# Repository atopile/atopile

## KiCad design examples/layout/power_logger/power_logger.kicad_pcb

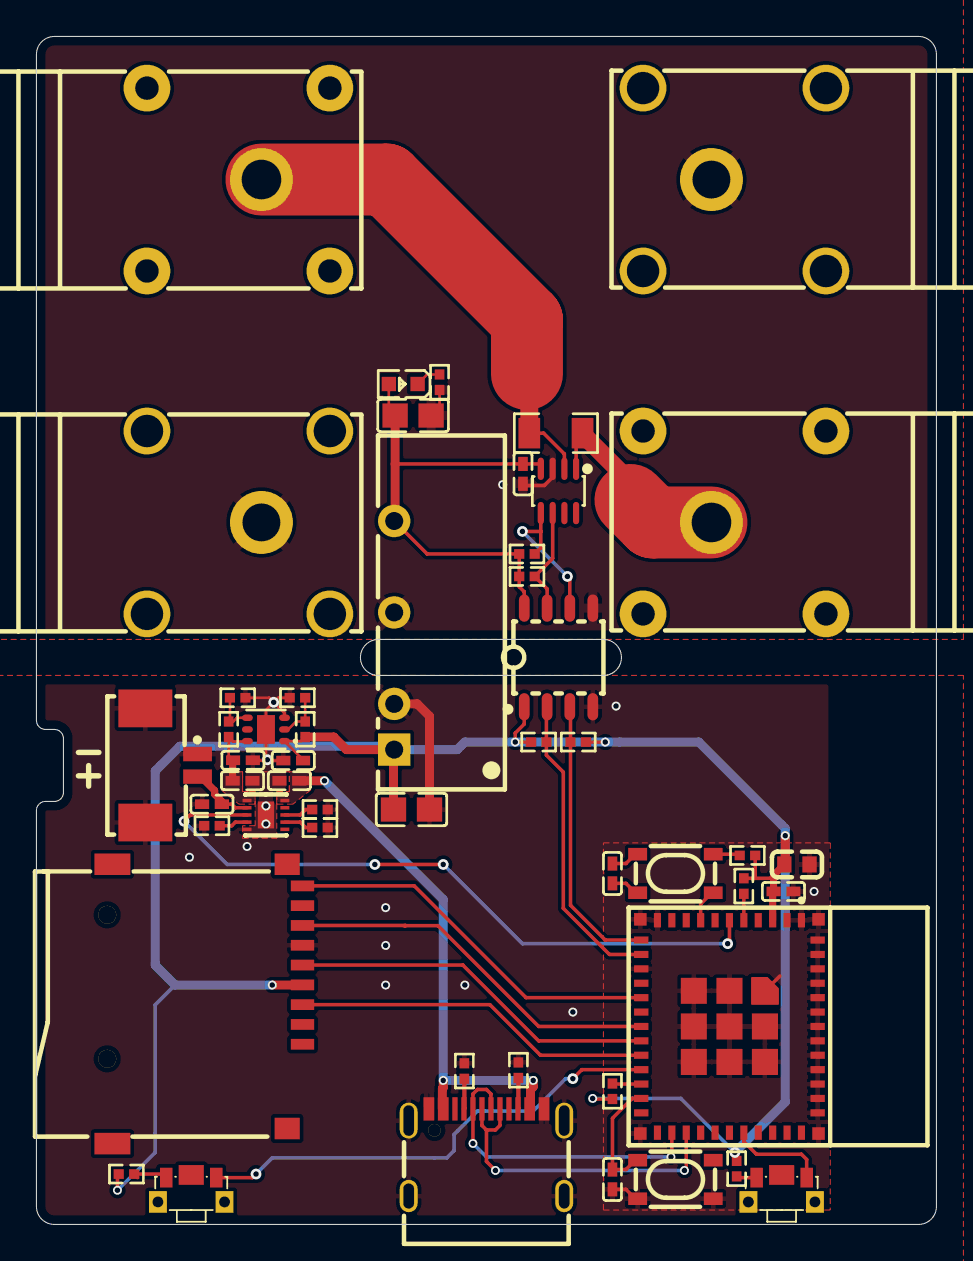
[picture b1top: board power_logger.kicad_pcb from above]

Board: 2 copper layers, 50.0 x 66.0 mm, 51 parts (1 on the bottom side), 38 nets.

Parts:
B1: EEMB_BATTERY_LP402535
C1, C3, C5, C6: 1µF ±10% 25V X5R; C0402
C2: 10µF ±20% 6.3V X5R; C0402
C4, C7, C8, C12: 100nF ±10% 16V X7R; C0402
C9: 22µF ±20% 6.3V X5R; C0603
C10: 2.2µF ±10% 25V X7R; C0805
C11: 10µF ±10% 25V X5R; C0805
Card1: TF-SMD_TF-01A
D1: LED0603-RD
J1, J3: ANT-TH_L33.0-W12.0_BLACK
J2, J4: ANT-TH_L33.0-W12.0_RED
R1, R2, R4, R5, R10, R11, R12, R13, R14, R15, R19, R20: 10kΩ ±1% 62.5mW; R0402
R3, R7: 100kΩ ±1% 62.5mW; R0402
R6: 0Ω 250mW; R1206
R8: 150kΩ ±1% 62.5mW; R0402
R9, R18: 2kΩ ±1% 62.5mW; R0402
R16, R17: 4.7kΩ ±1% 62.5mW; R0402
SW1, SW2: KEY-SMD_SKTDLDE010
SW3, SW4: KEY-SMD_4P-L4.2-W3.2-P2.20-LS4.6
U1: WSON-10_L2.2-W2.0-P0.40-BL-EP_TI_DLH0010A
U2: SOT-23-8_L2.9-W1.6-P0.65-LS2.8-BR
U3: WSON-6_L2.0-W2.0-P0.65-TL-EP
U4: WIFIM-SMD_ESP32-C3-MINI-1
U5: PWRM-TH_BXXXXS-2WR3
U6: SOIC-8_L4.9-W3.9-P1.27-LS6.0-TL
U7: CONN-SMD_532610271
USB1: USB-C-SMD_KH-TYPE-C-16P

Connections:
A5: R16.1, USB1.A5
B5: R17.1, USB1.B5
CD: Card1.9, U4.16
EN: R7.1, R8.2, U3.4
FB: R9.1, R10.2, U3.2
GND: Card1.10, Card1.11, Card1.12, Card1.13
ILIM_VSET: R3.1, U1.7
INneg: J4.5, R6.2, U2.2
INpos: J2.5, R6.1, U2.1
ISET: R1.1, U1.8
SCL2: R19.1, U2.5, U6.6
SDA2: R20.1, U2.6, U6.7
cathode: D1.1, R18.1
gnd: C1.2, C2.2, C3.2, C5.2, C6.2, C7.1, C9.2, C10.2, C12.2, Card1.6, R1.2, R2.2, R3.2, R7.2, R9.2, R16.2, R17.2, SW3.1, SW3.2, U1.5, U1.11, U3.3, U3.7, U4.1, U4.2, U4.11, U4.14, U4.36, U4.37, U4.38, U4.39, U4.40, U4.41, U4.42, U4.43, U4.44, U4.45, U4.46, U4.47, U4.48, U4.49, U4.50, U4.51, U4.52, U4.53, U5.2, U6.4, U7.1, U7.3, U7.4, USB1.1, USB1.2, USB1.3, USB1.4, USB1.A1, USB1.A12, USB1.B1, USB1.B12
gnd-1: C4.2, C11.2, J1.5, J3.5, R18.2, U2.3, U5.4, U6.5
hv: C5.1, C9.1, C10.1, C12.1, Card1.4, R4.2, R5.2, R10.1, R11.2, R12.2, R13.2, R14.2, R15.2, U3.1, U4.3, U5.1, U6.1
hv-1: C4.1, C11.1, D1.2, R19.2, R20.2, U2.4, U5.6, U6.8
hv-2: C3.1, U1.10, USB1.A4, USB1.A9, USB1.B4, USB1.B9
hv-3: C1.1, U1.2, U7.2
hv-4: C2.1, C6.1, R8.1, U1.1, U3.6
input: C8.1, R13.1, SW4.1, SW4.2
input-1: R5.1, SW2.1
input-2: R4.1, SW1.1
line: Card1.5, U4.19
line-1: Card1.3, U4.20
line-2: Card1.7, U4.18
line-3: R14.1, U4.12, U6.3
line-4: R15.1, U4.13, U6.2
line-5: R11.1, U4.5
line-6: U1.3, U4.6
line-7: U4.26, USB1.A7, USB1.B7
line-8: U4.27, USB1.A6, USB1.B6
line-10: R12.1, U4.22
nCE: R2.1, U1.4
output: C8.2, SW4.3, SW4.4, U4.8
output-1: SW2.2, U4.21
output-2: SW1.2, U4.31
output-3: C7.2, SW3.3, SW3.4, U4.23

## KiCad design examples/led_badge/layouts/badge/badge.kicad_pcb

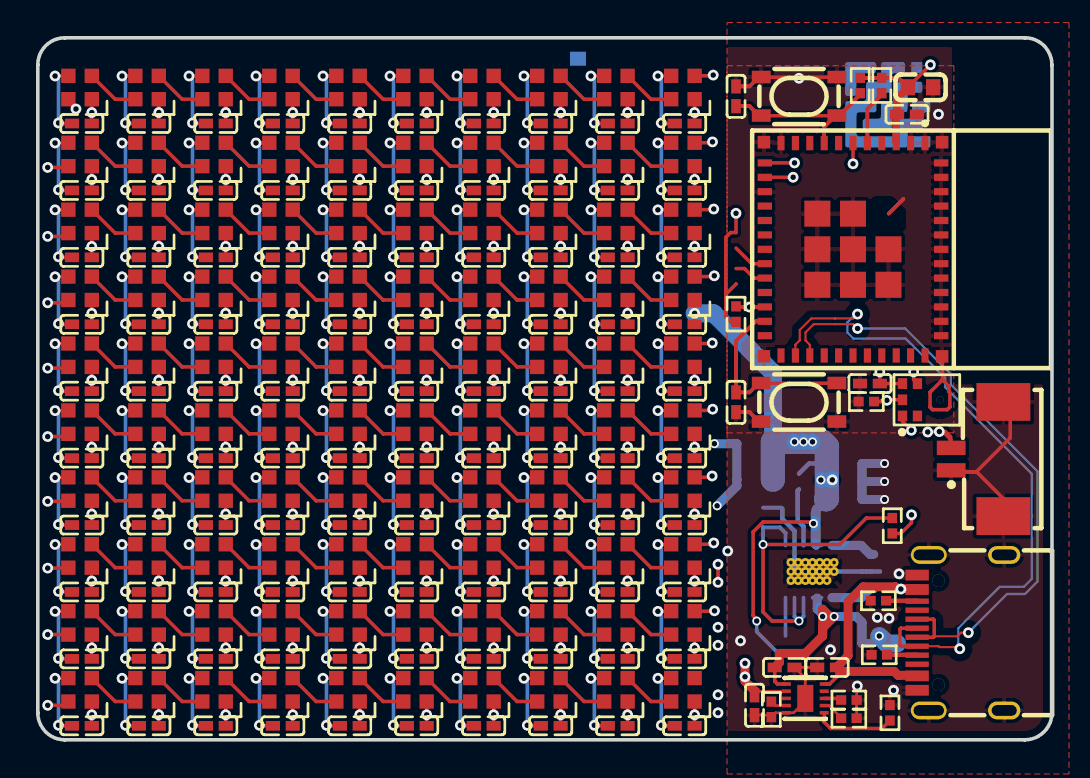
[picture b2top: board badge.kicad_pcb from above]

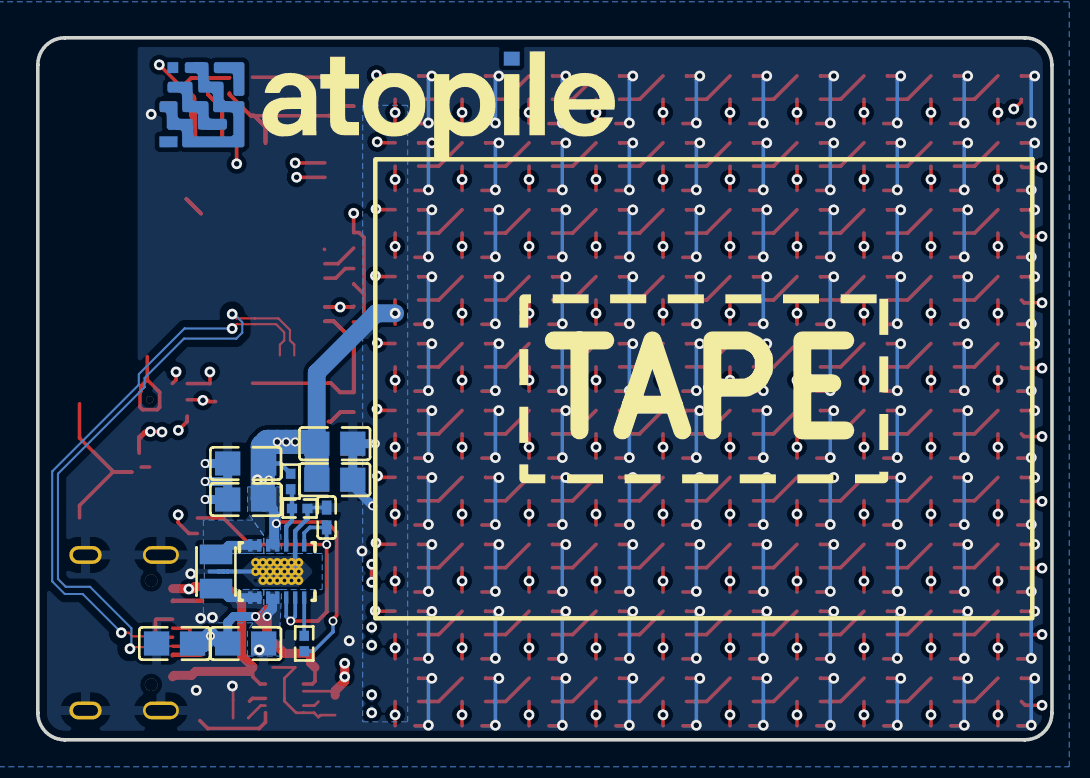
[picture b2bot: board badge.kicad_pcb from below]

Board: 4 copper layers, 56.3 x 39.0 mm, 240 parts (14 on the bottom side), 124 nets.

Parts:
B1: EEMB_BATTERY_LP402535
C1, C2: 10µF ±10% 25V X5R; C0805
C3, C4, C110, C111: 22µF ±20% 6.3V X5R; C0805
C5, C6, C7, C8, C9, C10, C11, C12, C13, C14, C15, C16, C17, C18, C19, C20, C21, C22, C23, C24, C25, C26, C27, C28, C29, C30, C31, C32, C33, C34, C35, C36, C37, C38, C39, C40, C41, C42, C43, C44, C45, C46, C47, C48, C49, C50, C51, C52, C53, C54, C55, C56, C57, C58, C59, C60, C61, C62, C63, C64, C65, C66, C67, C68, C69, C70, C71, C72, C73, C74, C75, C76, C77, C78, C79, C80, C81, C82, C83, C84, C85, C86, C87, C88, C89, C90, C91, C92, C93, C94, C95, C96, C97, C98, C99, C100, C101, C102, C103, C104, C105, C106, C107, C109, C112: 100nF ±10% 16V X7R; C0402
C108: 22µF ±20% 6.3V X5R; C0603
C113, C114: 1µF ±10% 25V X5R; C0402
C115: 10µF ±20% 6.3V X5R; C0402
L1: IND-SMD_L2.5-W2.0_WPN252012H
LED1, LED2, LED3, LED4, LED5, LED6, LED7, LED8, LED9, LED10, LED11, LED12, LED13, LED14, LED15, LED16, LED17, LED18, LED19, LED20, LED21, LED22, LED23, LED24, LED25, LED26, LED27, LED28, LED29, LED30, LED31, LED32, LED33, LED34, LED35, LED36, LED37, LED38, LED39, LED40, LED41, LED42, LED43, LED44, LED45, LED46, LED47, LED48, LED49, LED50, LED51, LED52, LED53, LED54, LED55, LED56, LED57, LED58, LED59, LED60, LED61, LED62, LED63, LED64, LED65, LED66, LED67, LED68, LED69, LED70, LED71, LED72, LED73, LED74, LED75, LED76, LED77, LED78, LED79, LED80, LED81, LED82, LED83, LED84, LED85, LED86, LED87, LED88, LED89, LED90, LED91, LED92, LED93, LED94, LED95, LED96, LED97, LED98, LED99, LED100: LED-SMD_4P-L2.0-W2.0-BR
LOGO1: atopile_Logo_25x6mm
R1: 200kΩ ±1% 62.5mW; R0402
R2, R3: 1MΩ ±1% 62.5mW; R0402
R4: 2kΩ ±1% 62.5mW; R0402
R5: 100kΩ ±1% 62.5mW; R0402
R6, R7, R8, R11, R13, R15: 10kΩ ±1% 62.5mW; R0402
R9, R10: 4.7kΩ ±1% 62.5mW; R0402
R12: 18kΩ ±1% 62.5mW; R0402
SW1, SW2: KEY-SMD_4P-L4.2-W3.2-P2.20-LS4.6
U2: CONN-SMD_532610271
U3: MIC-SMD_6P-L3.5-W2.7-P0.90-BL
U4: WIFIM-SMD_ESP32-C3-MINI-1
U5: WSON-10_L2.2-W2.0-P0.40-BL-EP_TI_DLH0010A
U6: VSON-14_L4.0-W3.0-P0.50-BL-EP_TI_DSJ
USB1: USB-C-SMD_KH-TYPE-C-16P

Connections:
A5: R9.1, USB1.A5
B5: R10.1, USB1.B5
ILIM_VSET: R12.1, U5.7
ISET: R4.1, U5.8
L1: L1.1, U6.8, U6.9
L2: L1.2, U6.6, U6.7
N_TRST: C107.2, R15.2, SW2.3, SW2.4, U4.8
PG: R3.1, U6.14
TS_MR: R13.1, U5.6
VCC: C112.1, R6.1, U6.1, U6.12, U6.13
VDIV_OUTPUT: R1.1, R2.2, U6.3
data_1: R7.1, U4.5
gnd: C1.2, C2.2, C3.2, C4.2, C5.2, C6.2, C7.2, C8.2, C9.2, C10.2, C11.2, C12.2, C13.2, C14.2, C15.2, C16.2, C17.2, C18.2, C19.2, C20.2, C21.2, C22.2, C23.2, C24.2, C25.2, C26.2, C27.2, C28.2, C29.2, C30.2, C31.2, C32.2, C33.2, C34.2, C35.2, C36.2, C37.2, C38.2, C39.2, C40.2, C41.2, C42.2, C43.2, C44.2, C45.2, C46.2, C47.2, C48.2, C49.2, C50.2, C51.2, C52.2, C53.2, C54.2, C55.2, C56.2, C57.2, C58.2, C59.2, C60.2, C61.2, C62.2, C63.2, C64.2, C65.2, C66.2, C67.2, C68.2, C69.2, C70.2, C71.2, C72.2, C73.2, C74.2, C75.2, C76.2, C77.2, C78.2, C79.2, C80.2, C81.2, C82.2, C83.2, C84.2, C85.2, C86.2, C87.2, C88.2, C89.2, C90.2, C91.2, C92.2, C93.2, C94.2, C95.2, C96.2, C97.2, C98.2, C99.2, C100.2, C101.2, C102.2, C103.2, C104.2, C105.2, C106.1, C107.1, C108.2, C109.2, C110.2, C111.2, C112.2, C113.2, C114.2, C115.2, LED1.3, LED2.3, LED3.3, LED4.3, LED5.3, LED6.3, LED7.3, LED8.3, LED9.3, LED10.3, LED11.3, LED12.3, LED13.3, LED14.3, LED15.3, LED16.3, LED17.3, LED18.3, LED19.3, LED20.3, LED21.3, LED22.3, LED23.3, LED24.3, LED25.3, LED26.3, LED27.3, LED28.3, LED29.3, LED30.3, LED31.3, LED32.3, LED33.3, LED34.3, LED35.3, LED36.3, LED37.3, LED38.3, LED39.3, LED40.3, LED41.3, LED42.3, LED43.3, LED44.3, LED45.3, LED46.3, LED47.3, LED48.3, LED49.3, LED50.3, LED51.3, LED52.3, LED53.3, LED54.3, LED55.3, LED56.3, LED57.3, LED58.3, LED59.3, LED60.3, LED61.3, LED62.3, LED63.3, LED64.3, LED65.3, LED66.3, LED67.3, LED68.3, LED69.3, LED70.3, LED71.3, LED72.3, LED73.3, LED74.3, LED75.3, LED76.3, LED77.3, LED78.3, LED79.3, LED80.3, LED81.3, LED82.3, LED83.3, LED84.3, LED85.3, LED86.3, LED87.3, LED88.3, LED89.3, LED90.3, LED91.3, LED92.3, LED93.3, LED94.3, LED95.3, LED96.3, LED97.3, LED98.3, LED99.3, LED100.3, R1.2, R4.2, R5.2, R9.2, R10.2, R11.2, R12.2, R13.2, SW1.1, SW1.2, SW2.1, SW2.2, U2.1, U2.3, U2.4, U3.3, U4.1, U4.2, U4.11, U4.14, U4.36, U4.37, U4.38, U4.39, U4.40, U4.41, U4.42, U4.43, U4.44, U4.45, U4.46, U4.47, U4.48, U4.49, U4.50, U4.51, U4.52, U4.53, U5.5, U5.11, U6.2, U6.15, USB1.1, USB1.2, USB1.3, USB1.4, USB1.A1, USB1.A12, USB1.B1, USB1.B12
i2s_sck: U3.4, U4.12
i2s_sd: R5.1, U3.6, U4.13
i2s_ws: U3.1, U4.6
led_data: LED1.4, R8.1, U4.22
leds[1]-data_in-DIN-0: LED1.2, LED2.4
leds[1]-data_in-DIN-1: LED11.2, LED12.4
leds[1]-data_in-DIN-2: LED21.2, LED22.4
leds[1]-data_in-DIN-3: LED31.2, LED32.4
leds[1]-data_in-DIN-4: LED41.2, LED42.4
leds[1]-data_in-DIN-5: LED51.2, LED52.4
leds[1]-data_in-DIN-6: LED61.2, LED62.4
leds[1]-data_in-DIN-7: LED71.2, LED72.4
leds[1]-data_in-DIN-8: LED81.2, LED82.4
leds[1]-data_in-DIN-9: LED91.2, LED92.4
leds[2]-data_in-DIN-0: LED2.2, LED3.4
leds[2]-data_in-DIN-1: LED12.2, LED13.4
leds[2]-data_in-DIN-2: LED22.2, LED23.4
leds[2]-data_in-DIN-3: LED32.2, LED33.4
leds[2]-data_in-DIN-4: LED42.2, LED43.4
leds[2]-data_in-DIN-5: LED52.2, LED53.4
leds[2]-data_in-DIN-6: LED62.2, LED63.4
leds[2]-data_in-DIN-7: LED72.2, LED73.4
leds[2]-data_in-DIN-8: LED82.2, LED83.4
leds[2]-data_in-DIN-9: LED92.2, LED93.4
leds[3]-data_in-DIN-0: LED3.2, LED4.4
leds[3]-data_in-DIN-1: LED13.2, LED14.4
leds[3]-data_in-DIN-2: LED23.2, LED24.4
leds[3]-data_in-DIN-3: LED33.2, LED34.4
leds[3]-data_in-DIN-4: LED43.2, LED44.4
leds[3]-data_in-DIN-5: LED53.2, LED54.4
leds[3]-data_in-DIN-6: LED63.2, LED64.4
leds[3]-data_in-DIN-7: LED73.2, LED74.4
leds[3]-data_in-DIN-8: LED83.2, LED84.4
leds[3]-data_in-DIN-9: LED93.2, LED94.4
leds[4]-data_in-DIN-0: LED4.2, LED5.4
leds[4]-data_in-DIN-1: LED14.2, LED15.4
leds[4]-data_in-DIN-2: LED24.2, LED25.4
leds[4]-data_in-DIN-3: LED34.2, LED35.4
leds[4]-data_in-DIN-4: LED44.2, LED45.4
leds[4]-data_in-DIN-5: LED54.2, LED55.4
leds[4]-data_in-DIN-6: LED64.2, LED65.4
leds[4]-data_in-DIN-7: LED74.2, LED75.4
leds[4]-data_in-DIN-8: LED84.2, LED85.4
leds[4]-data_in-DIN-9: LED94.2, LED95.4
leds[5]-data_in-DIN-0: LED5.2, LED6.4
leds[5]-data_in-DIN-1: LED15.2, LED16.4
leds[5]-data_in-DIN-2: LED25.2, LED26.4
leds[5]-data_in-DIN-3: LED35.2, LED36.4
leds[5]-data_in-DIN-4: LED45.2, LED46.4
leds[5]-data_in-DIN-5: LED55.2, LED56.4
leds[5]-data_in-DIN-6: LED65.2, LED66.4
leds[5]-data_in-DIN-7: LED75.2, LED76.4
leds[5]-data_in-DIN-8: LED85.2, LED86.4
leds[5]-data_in-DIN-9: LED95.2, LED96.4
leds[6]-data_in-DIN-0: LED6.2, LED7.4
leds[6]-data_in-DIN-1: LED16.2, LED17.4
leds[6]-data_in-DIN-2: LED26.2, LED27.4
leds[6]-data_in-DIN-3: LED36.2, LED37.4
leds[6]-data_in-DIN-4: LED46.2, LED47.4
leds[6]-data_in-DIN-5: LED56.2, LED57.4
leds[6]-data_in-DIN-6: LED66.2, LED67.4
leds[6]-data_in-DIN-7: LED76.2, LED77.4
leds[6]-data_in-DIN-8: LED86.2, LED87.4
leds[6]-data_in-DIN-9: LED96.2, LED97.4
leds[7]-data_in-DIN-0: LED7.2, LED8.4
leds[7]-data_in-DIN-1: LED17.2, LED18.4
leds[7]-data_in-DIN-2: LED27.2, LED28.4
leds[7]-data_in-DIN-3: LED37.2, LED38.4
leds[7]-data_in-DIN-4: LED47.2, LED48.4
leds[7]-data_in-DIN-5: LED57.2, LED58.4
leds[7]-data_in-DIN-6: LED67.2, LED68.4
leds[7]-data_in-DIN-7: LED77.2, LED78.4
leds[7]-data_in-DIN-8: LED87.2, LED88.4
leds[7]-data_in-DIN-9: LED97.2, LED98.4
leds[8]-data_in-DIN-0: LED8.2, LED9.4
leds[8]-data_in-DIN-1: LED18.2, LED19.4
leds[8]-data_in-DIN-2: LED28.2, LED29.4
leds[8]-data_in-DIN-3: LED38.2, LED39.4
leds[8]-data_in-DIN-4: LED48.2, LED49.4
leds[8]-data_in-DIN-5: LED58.2, LED59.4
leds[8]-data_in-DIN-6: LED68.2, LED69.4
leds[8]-data_in-DIN-7: LED78.2, LED79.4
leds[8]-data_in-DIN-8: LED88.2, LED89.4
leds[8]-data_in-DIN-9: LED98.2, LED99.4
leds[9]-data_in-DIN-0: LED9.2, LED10.4
leds[9]-data_in-DIN-1: LED19.2, LED20.4
leds[9]-data_in-DIN-2: LED29.2, LED30.4
leds[9]-data_in-DIN-3: LED39.2, LED40.4
leds[9]-data_in-DIN-4: LED49.2, LED50.4
leds[9]-data_in-DIN-5: LED59.2, LED60.4
leds[9]-data_in-DIN-6: LED69.2, LED70.4
leds[9]-data_in-DIN-7: LED79.2, LED80.4
leds[9]-data_in-DIN-8: LED89.2, LED90.4
leds[9]-data_in-DIN-9: LED99.2, LED100.4
nCE: R11.1, U5.4
output: C106.2, SW1.3, SW1.4, U4.23
power_3v3: C3.1, C4.1, C5.1, C6.1, C7.1, C8.1, C9.1, C10.1, C11.1, C12.1, C13.1, C14.1, C15.1, C16.1, C17.1, C18.1, C19.1, C20.1, C21.1, C22.1, C23.1, C24.1, C25.1, C26.1, C27.1, C28.1, C29.1, C30.1, C31.1, C32.1, C33.1, C34.1, C35.1, C36.1, C37.1, C38.1, C39.1, C40.1, C41.1, C42.1, C43.1, C44.1, C45.1, C46.1, C47.1, C48.1, C49.1, C50.1, C51.1, C52.1, C53.1, C54.1, C55.1, C56.1, C57.1, C58.1, C59.1, C60.1, C61.1, C62.1, C63.1, C64.1, C65.1, C66.1, C67.1, C68.1, C69.1, C70.1, C71.1, C72.1, C73.1, C74.1, C75.1, C76.1, C77.1, C78.1, C79.1, C80.1, C81.1, C82.1, C83.1, C84.1, C85.1, C86.1, C87.1, C88.1, C89.1, C90.1, C91.1, C92.1, C93.1, C94.1, C95.1, C96.1, C97.1, C98.1, C99.1, C100.1, C101.1, C102.1, C103.1, C104.1, C105.1, C108.1, C109.1, C110.1, C111.1, LED1.1, LED2.1, LED3.1, LED4.1, LED5.1, LED6.1, LED7.1, LED8.1, LED9.1, LED10.1, LED11.1, LED12.1, LED13.1, LED14.1, LED15.1, LED16.1, LED17.1, LED18.1, LED19.1, LED20.1, LED21.1, LED22.1, LED23.1, LED24.1, LED25.1, LED26.1, LED27.1, LED28.1, LED29.1, LED30.1, LED31.1, LED32.1, LED33.1, LED34.1, LED35.1, LED36.1, LED37.1, LED38.1, LED39.1, LED40.1, LED41.1, LED42.1, LED43.1, LED44.1, LED45.1, LED46.1, LED47.1, LED48.1, LED49.1, LED50.1, LED51.1, LED52.1, LED53.1, LED54.1, LED55.1, LED56.1, LED57.1, LED58.1, LED59.1, LED60.1, LED61.1, LED62.1, LED63.1, LED64.1, LED65.1, LED66.1, LED67.1, LED68.1, LED69.1, LED70.1, LED71.1, LED72.1, LED73.1, LED74.1, LED75.1, LED76.1, LED77.1, LED78.1, LED79.1, LED80.1, LED81.1, LED82.1, LED83.1, LED84.1, LED85.1, LED86.1, LED87.1, LED88.1, LED89.1, LED90.1, LED91.1, LED92.1, LED93.1, LED94.1, LED95.1, LED96.1, LED97.1, LED98.1, LED99.1, LED100.1, R2.1, R3.2, R7.2, R8.2, R15.1, U3.5, U4.3, U6.4, U6.5
power_battery: C113.1, U2.2, U5.2
power_system: C1.1, C2.1, C115.1, U5.1, U6.10, U6.11
rows[1]-data_in-line: LED10.2, LED11.4
rows[2]-data_in-line: LED20.2, LED21.4
rows[3]-data_in-line: LED30.2, LED31.4
rows[4]-data_in-line: LED40.2, LED41.4
rows[5]-data_in-line: LED50.2, LED51.4
rows[6]-data_in-line: LED60.2, LED61.4
rows[7]-data_in-line: LED70.2, LED71.4
rows[8]-data_in-line: LED80.2, LED81.4
rows[9]-data_in-line: LED90.2, LED91.4
usb_N: U4.26, USB1.A7, USB1.B7
usb_P: U4.27, USB1.A6, USB1.B6
usb_power: C114.1, R6.2, U5.10, USB1.A4, USB1.A9, USB1.B4, USB1.B9

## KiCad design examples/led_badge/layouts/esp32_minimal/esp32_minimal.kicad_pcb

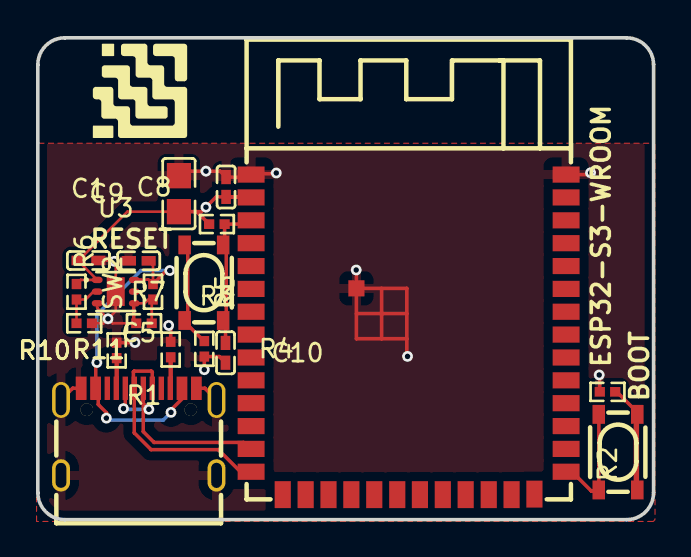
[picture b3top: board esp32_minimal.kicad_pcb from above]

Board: 2 copper layers, 34.2 x 26.8 mm, 19 parts (0 on the bottom side), 13 nets.

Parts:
C1, C5, C10: 1µF ±10% 25V X5R; C0402
C8: 100nF ±10% 16V X7R; C0402
C9: 22µF ±20% 6.3V X5R; C0805
R1: 47kΩ ±1% 62.5mW; R0402
R2, R4: 100Ω ±1% 62.5mW; R0402
R3, R7: 10kΩ ±1% 62.5mW; R0402
R5: 150kΩ ±1% 62.5mW; R0402
R6: 2kΩ ±1% 62.5mW; R0402
R10, R11: 4.7kΩ ±1% 62.5mW; R0402
SW1, SW2: KEY-SMD_4P-L4.2-W3.2-P2.20-LS4.6
U2: WIRELM-SMD_ESP32-S3-WROOM-1
U3: WSON-6_L2.0-W2.0-P0.65-TL-EP
USB1: USB-C-SMD_KH-TYPE-C-16P

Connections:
A5: R10.1, USB1.A5
B5: R11.1, USB1.B5
EN: R1.1, R5.2, U3.4
FB: R6.1, R7.2, U3.2
gnd: C1.2, C5.2, C8.2, C9.2, C10.2, R1.2, R2.2, R4.2, R6.2, R10.2, R11.2, U2.1, U2.40, U2.41, U3.3, U3.7, USB1.1, USB1.2, USB1.3, USB1.4, USB1.A1, USB1.A12, USB1.B1, USB1.B12
hv: C5.1, R5.1, U3.6, USB1.A4, USB1.A9, USB1.B4, USB1.B9
hv-1: C1.1, C8.1, C9.1, R3.2, R7.1, U2.2, U3.1
input: R2.1, SW1.1, SW1.2
input-1: R4.1, SW2.1, SW2.2
line: U2.13, USB1.A7, USB1.B7
line-1: U2.14, USB1.A6, USB1.B6
output: SW1.3, SW1.4, U2.27
output-1: C10.1, R3.1, SW2.3, SW2.4, U2.3

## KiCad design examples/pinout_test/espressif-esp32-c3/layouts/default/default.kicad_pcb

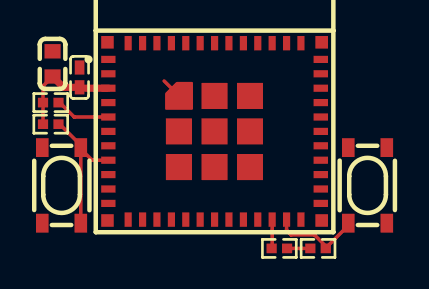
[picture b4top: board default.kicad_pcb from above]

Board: 2 copper layers, 9 parts (0 on the bottom side), 6 nets.

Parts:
C3: 22µF ±20% 6.3V X5R; C0603
C4: 100nF ±10% 16V X7R; C0402
R1, R2, R3: 10kΩ ±1% 62.5mW; R0402
R4: 5.1kΩ ±1% 62.5mW; R0402
SW1, SW2: KEY-SMD_4P-L4.2-W3.2-P2.20-LS4.6
U1: WIFIM-SMD_ESP32-C3-MINI-1

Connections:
GND: C3.2, C4.2, SW1.1, SW1.2, SW2.1, SW2.2, U1.1, U1.2, U1.11, U1.14, U1.36, U1.37, U1.38, U1.39, U1.40, U1.41, U1.42, U1.43, U1.44, U1.45, U1.46, U1.47, U1.48, U1.49, U1.50, U1.51, U1.52, U1.53
MISO: R2.1, U1.22
N_TRST: R3.2, SW2.3, SW2.4, U1.8
VCC: C3.1, C4.1, R1.2, R2.2, R3.1, R4.1, U1.3
data_1: R1.1, U1.5
output: R4.2, SW1.3, SW1.4, U1.23
